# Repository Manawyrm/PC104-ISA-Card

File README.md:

# PC104-ISA-Card

Adapter for connecting a PC104 computer to a 16-bit ISA backplane.  
Power can be supplied from the backplane or from the PC104 module itself.  
DMA and IRQs are supported. Optional support for power filtering capacitors on the PCB is present.

## Status

RevA is fully functional and works well.

## Attribution

[sur5r](https://github.com/sur5r) - Schematic, mechanical design, initial PCB layout  

[Manawyrm](https://github.com/Manawyrm) - PCB layout/routing

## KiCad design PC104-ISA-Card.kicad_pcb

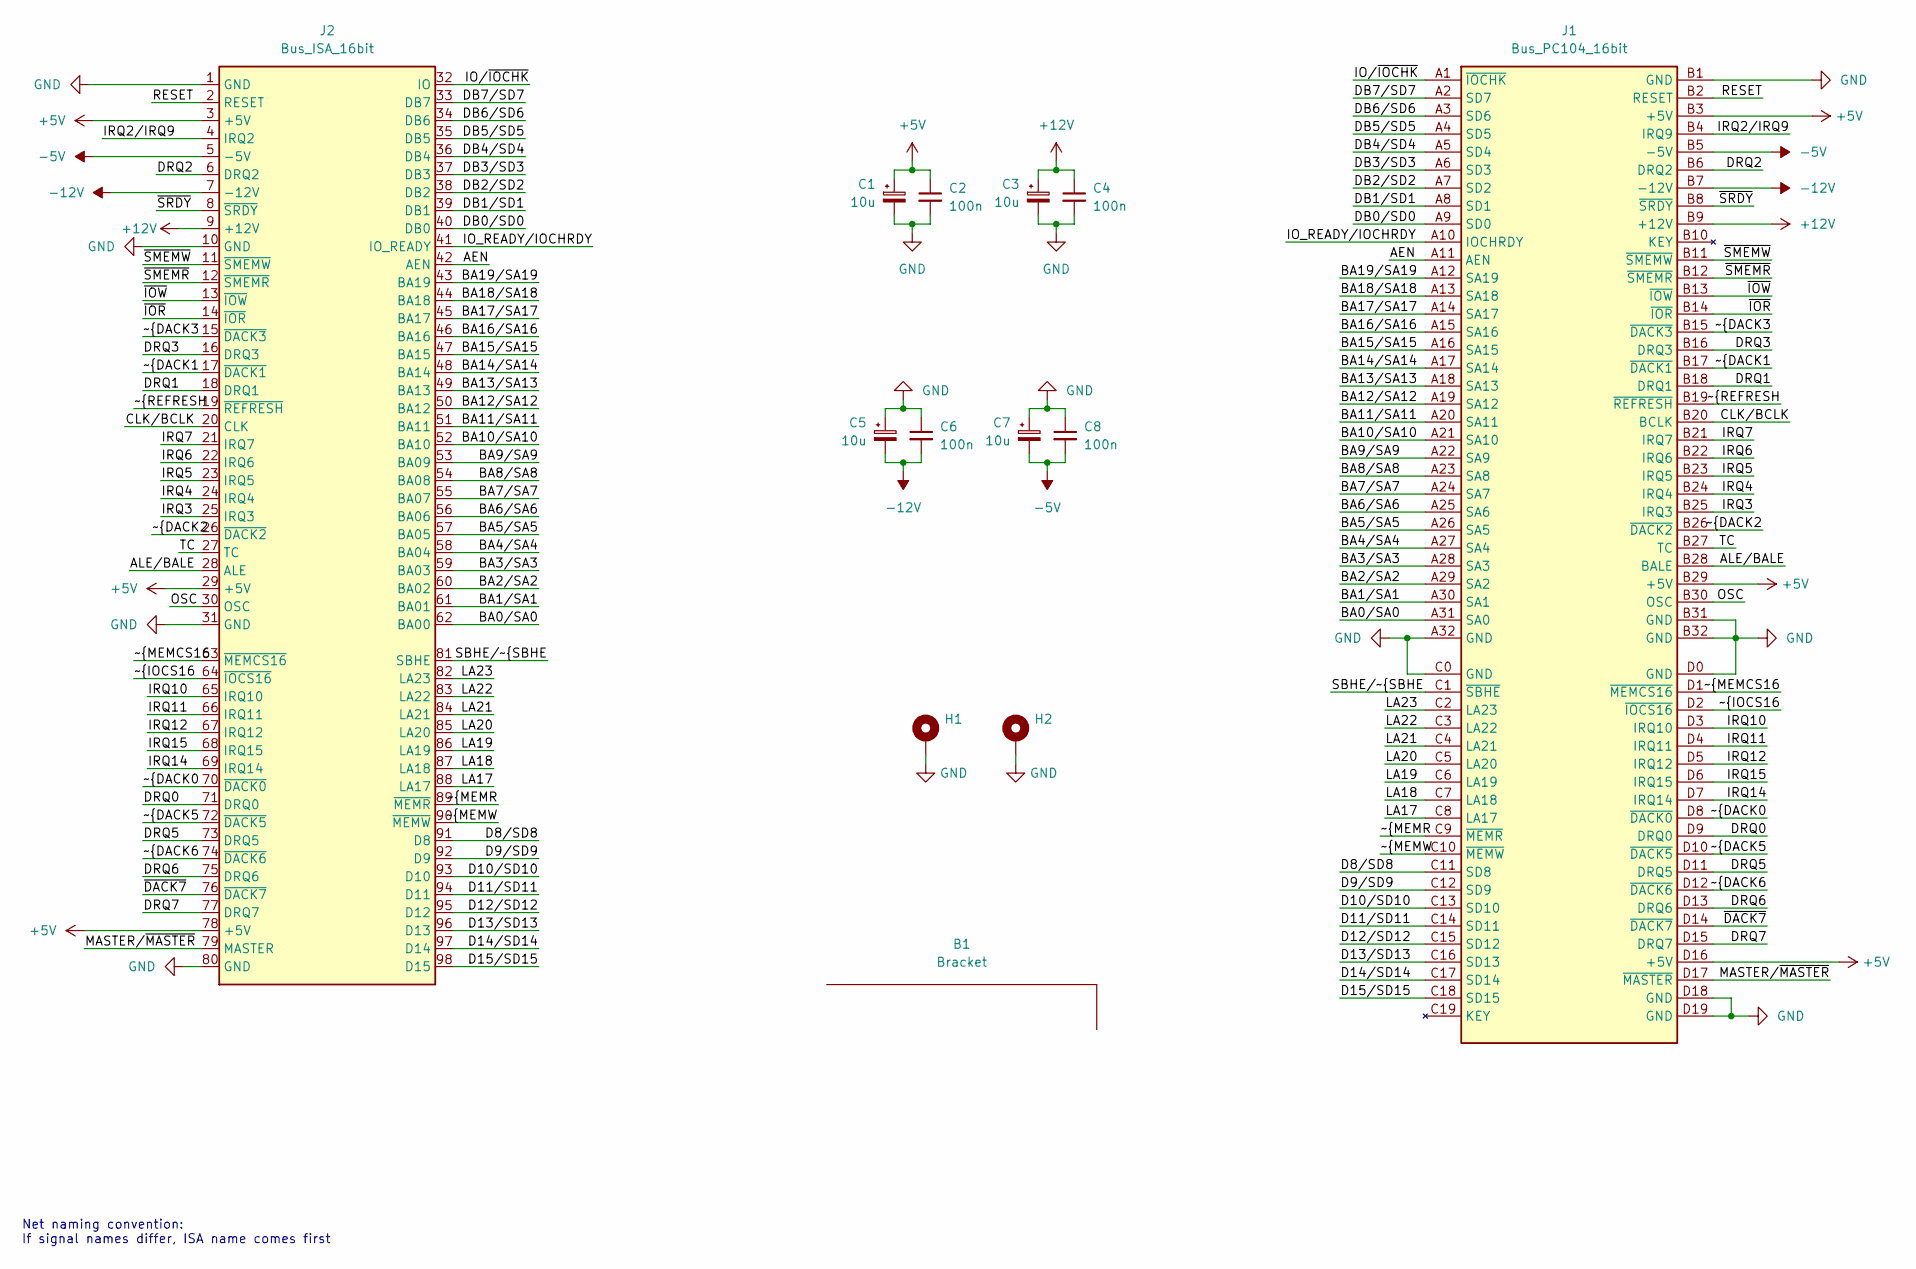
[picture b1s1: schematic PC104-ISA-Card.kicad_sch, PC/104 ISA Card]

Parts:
B1: Bracket; MPN 9202
C1, C3, C5, C7: 10u; CP_EIA-7343-15_Kemet-W
C2, C4, C6, C8: 100n; C_0603_1608Metric
H1, H2: MountingHole_3.2mm_M3_Pad_Via
J1: Bus_PC104_16bit; PC104_16bit
J2: Bus_ISA_16bit; BUS_AT

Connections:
+5V: C1.1, C2.1, J1.B3 (+5V), J1.B29 (+5V), J1.D16 (+5V), J2.3 (+5V), J2.29 (+5V), J2.78 (+5V)
+12V: C3.1, C4.1, J1.B9 (+12V), J2.9 (+12V)
-5V: C7.2, C8.2, J1.B5 (-5V), J2.5 (-5V)
-12V: C5.2, C6.2, J1.B7 (-12V), J2.7 (-12V)
/AEN: J1.A11 (AEN), J2.42 (AEN)
/ALE/BALE: J1.B28 (BALE), J2.28 (ALE)
/BA0/SA0: J1.A31 (SA0), J2.62 (BA00)
/BA1/SA1: J1.A30 (SA1), J2.61 (BA01)
/BA2/SA2: J1.A29 (SA2), J2.60 (BA02)
/BA3/SA3: J1.A28 (SA3), J2.59 (BA03)
/BA4/SA4: J1.A27 (SA4), J2.58 (BA04)
/BA5/SA5: J1.A26 (SA5), J2.57 (BA05)
/BA6/SA6: J1.A25 (SA6), J2.56 (BA06)
/BA7/SA7: J1.A24 (SA7), J2.55 (BA07)
/BA8/SA8: J1.A23 (SA8), J2.54 (BA08)
/BA9/SA9: J1.A22 (SA9), J2.53 (BA09)
/BA10/SA10: J1.A21 (SA10), J2.52 (BA10)
/BA11/SA11: J1.A20 (SA11), J2.51 (BA11)
/BA12/SA12: J1.A19 (SA12), J2.50 (BA12)
/BA13/SA13: J1.A18 (SA13), J2.49 (BA13)
/BA14/SA14: J1.A17 (SA14), J2.48 (BA14)
/BA15/SA15: J1.A16 (SA15), J2.47 (BA15)
/BA16/SA16: J1.A15 (SA16), J2.46 (BA16)
/BA17/SA17: J1.A14 (SA17), J2.45 (BA17)
/BA18/SA18: J1.A13 (SA18), J2.44 (BA18)
/BA19/SA19: J1.A12 (SA19), J2.43 (BA19)
/CLK/BCLK: J1.B20 (BCLK), J2.20 (CLK)
/D8/SD8: J1.C11 (SD8), J2.91 (D8)
/D9/SD9: J1.C12 (SD9), J2.92 (D9)
/D10/SD10: J1.C13 (SD10), J2.93 (D10)
/D11/SD11: J1.C14 (SD11), J2.94 (D11)
/D12/SD12: J1.C15 (SD12), J2.95 (D12)
/D13/SD13: J1.C16 (SD13), J2.96 (D13)
/D14/SD14: J1.C17 (SD14), J2.97 (D14)
/D15/SD15: J1.C18 (SD15), J2.98 (D15)
/DB0/SD0: J1.A9 (SD0), J2.40 (DB0)
/DB1/SD1: J1.A8 (SD1), J2.39 (DB1)
/DB2/SD2: J1.A7 (SD2), J2.38 (DB2)
/DB3/SD3: J1.A6 (SD3), J2.37 (DB3)
/DB4/SD4: J1.A5 (SD4), J2.36 (DB4)
/DB5/SD5: J1.A4 (SD5), J2.35 (DB5)
/DB6/SD6: J1.A3 (SD6), J2.34 (DB6)
/DB7/SD7: J1.A2 (SD7), J2.33 (DB7)
/DRQ0: J1.D9 (DRQ0), J2.71 (DRQ0)
/DRQ1: J1.B18 (DRQ1), J2.18 (DRQ1)
/DRQ2: J1.B6 (DRQ2), J2.6 (DRQ2)
/DRQ3: J1.B16 (DRQ3), J2.16 (DRQ3)
/DRQ5: J1.D11 (DRQ5), J2.73 (DRQ5)
/DRQ6: J1.D13 (DRQ6), J2.75 (DRQ6)
/DRQ7: J1.D15 (DRQ7), J2.77 (DRQ7)
/IO_READY/IOCHRDY: J1.A10 (IOCHRDY), J2.41 (IO_READY)
/IO/~IOCHK: J1.A1 (~IOCHK), J2.32 (IO)
/IRQ2/IRQ9: J1.B4 (IRQ9), J2.4 (IRQ2)
/IRQ3: J1.B25 (IRQ3), J2.25 (IRQ3)
/IRQ4: J1.B24 (IRQ4), J2.24 (IRQ4)
/IRQ5: J1.B23 (IRQ5), J2.23 (IRQ5)
/IRQ6: J1.B22 (IRQ6), J2.22 (IRQ6)
/IRQ7: J1.B21 (IRQ7), J2.21 (IRQ7)
/IRQ10: J1.D3 (IRQ10), J2.65 (IRQ10)
/IRQ11: J1.D4 (IRQ11), J2.66 (IRQ11)
/IRQ12: J1.D5 (IRQ12), J2.67 (IRQ12)
/IRQ14: J1.D7 (IRQ14), J2.69 (IRQ14)
/IRQ15: J1.D6 (IRQ15), J2.68 (IRQ15)
/LA17: J1.C8 (LA17), J2.88 (LA17)
/LA18: J1.C7 (LA18), J2.87 (LA18)
/LA19: J1.C6 (LA19), J2.86 (LA19)
/LA20: J1.C5 (LA20), J2.85 (LA20)
/LA21: J1.C4 (LA21), J2.84 (LA21)
/LA22: J1.C3 (LA22), J2.83 (LA22)
/LA23: J1.C2 (LA23), J2.82 (LA23)
/MASTER/~MASTER: J1.D17 (~MASTER), J2.79 (MASTER)
/OSC: J1.B30 (OSC), J2.30 (OSC)
/RESET: J1.B2 (RESET), J2.2 (RESET)
/SBHE/~SBHE: J1.C1 (~SBHE), J2.81 (SBHE)
/TC: J1.B27 (TC), J2.27 (TC)
/~DACK0: J1.D8 (~DACK0), J2.70 (~DACK0)
/~DACK1: J1.B17 (~DACK1), J2.17 (~DACK1)
/~DACK2: J1.B26 (~DACK2), J2.26 (~DACK2)
/~DACK3: J1.B15 (~DACK3), J2.15 (~DACK3)
/~DACK5: J1.D10 (~DACK5), J2.72 (~DACK5)
/~DACK6: J1.D12 (~DACK6), J2.74 (~DACK6)
/~DACK7: J1.D14 (~DACK7), J2.76 (~DACK7)
/~IOCS16: J1.D2 (~IOCS16), J2.64 (~IOCS16)
/~IOR: J1.B14 (~IOR), J2.14 (~IOR)
/~IOW: J1.B13 (~IOW), J2.13 (~IOW)
/~MEMCS16: J1.D1 (~MEMCS16), J2.63 (~MEMCS16)
/~MEMR: J1.C9 (~MEMR), J2.89 (~MEMR)
/~MEMW: J1.C10 (~MEMW), J2.90 (~MEMW)
/~REFRESH: J1.B19 (~REFRESH), J2.19 (~REFRESH)
/~SMEMR: J1.B12 (~SMEMR), J2.12 (~SMEMR)
/~SMEMW: J1.B11 (~SMEMW), J2.11 (~SMEMW)
/~SRDY: J1.B8 (~SRDY), J2.8 (~SRDY)
GND: C1.2, C2.2, C3.2, C4.2, C5.1, C6.1, C7.1, C8.1, H1.1, H2.1, J1.A32 (GND), J1.B1 (GND), J1.B31 (GND), J1.B32 (GND), J1.C0 (GND), J1.D0 (GND), J1.D18 (GND), J1.D19 (GND), J2.1 (GND), J2.10 (GND), J2.31 (GND), J2.80 (GND)

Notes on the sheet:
Net naming convention: If signal names differ, ISA name comes first

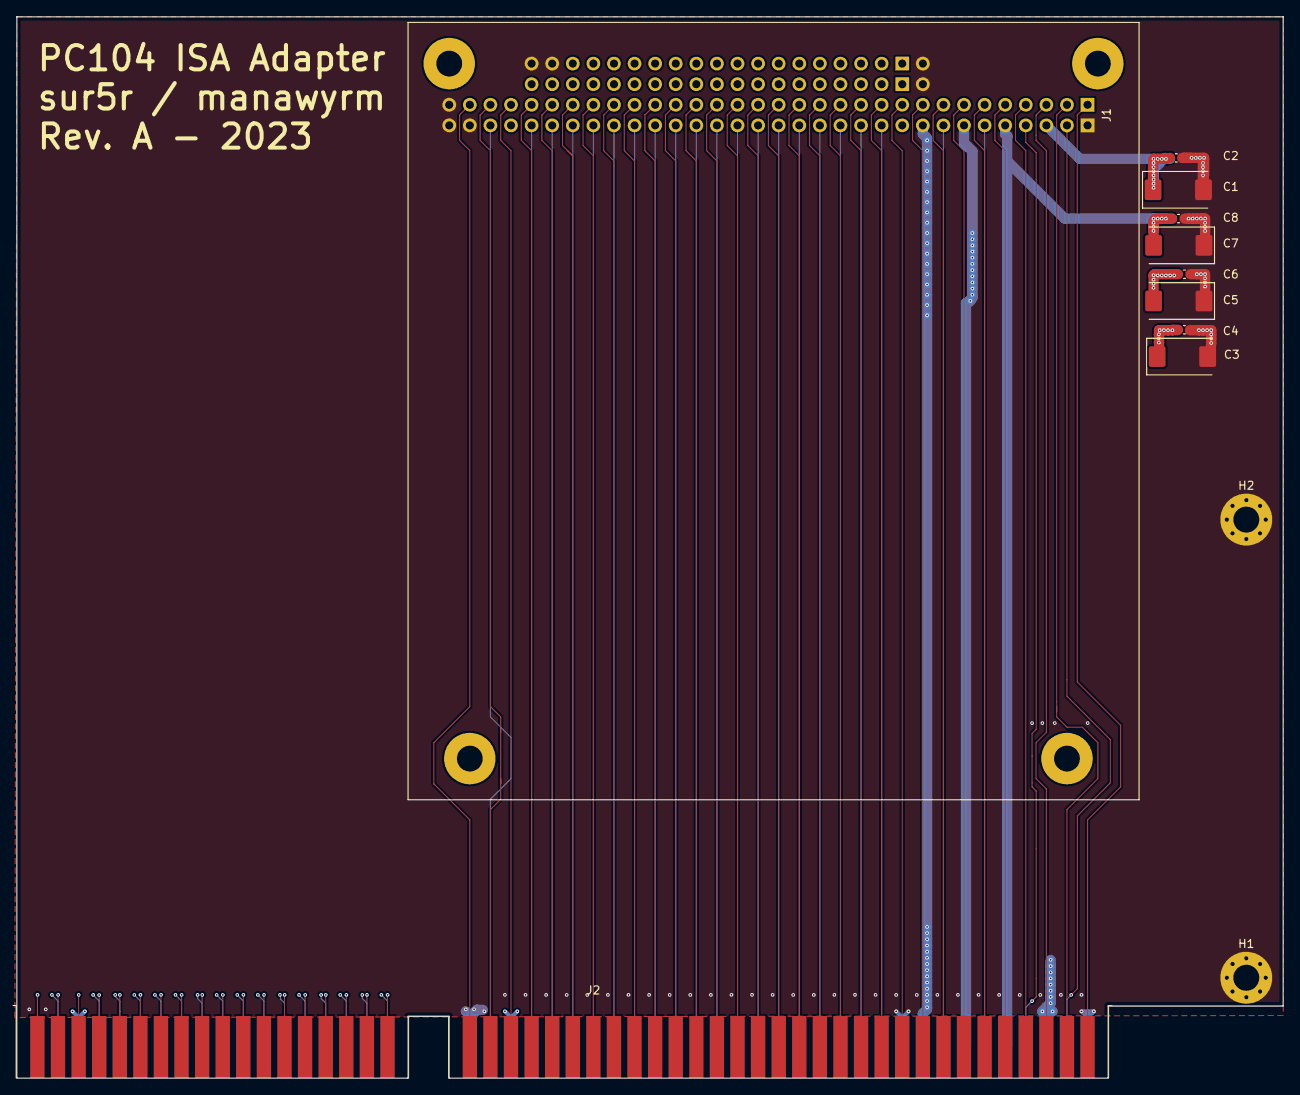
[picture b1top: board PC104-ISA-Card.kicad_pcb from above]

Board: 4 copper layers, 156.2 x 130.9 mm, 12 parts (0 on the bottom side), 93 nets.

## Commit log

2023-03-04 Move mounting holes to correct place for Keystone 9202
2023-03-04 Reduce board height
2023-03-04 Add bracket symbol
2023-03-04 Fix pin number typo
2023-03-04 Preliminary schematic
2023-03-04 Fix SRDY pin details
2023-03-26 Layout WIP
2023-03-26 Release this under CERN OHL-S Version 2
2023-03-27 Added layout
2023-03-27 Fix ISA slot grounding
2023-04-11 Add gerbers
2023-04-17 Add README
